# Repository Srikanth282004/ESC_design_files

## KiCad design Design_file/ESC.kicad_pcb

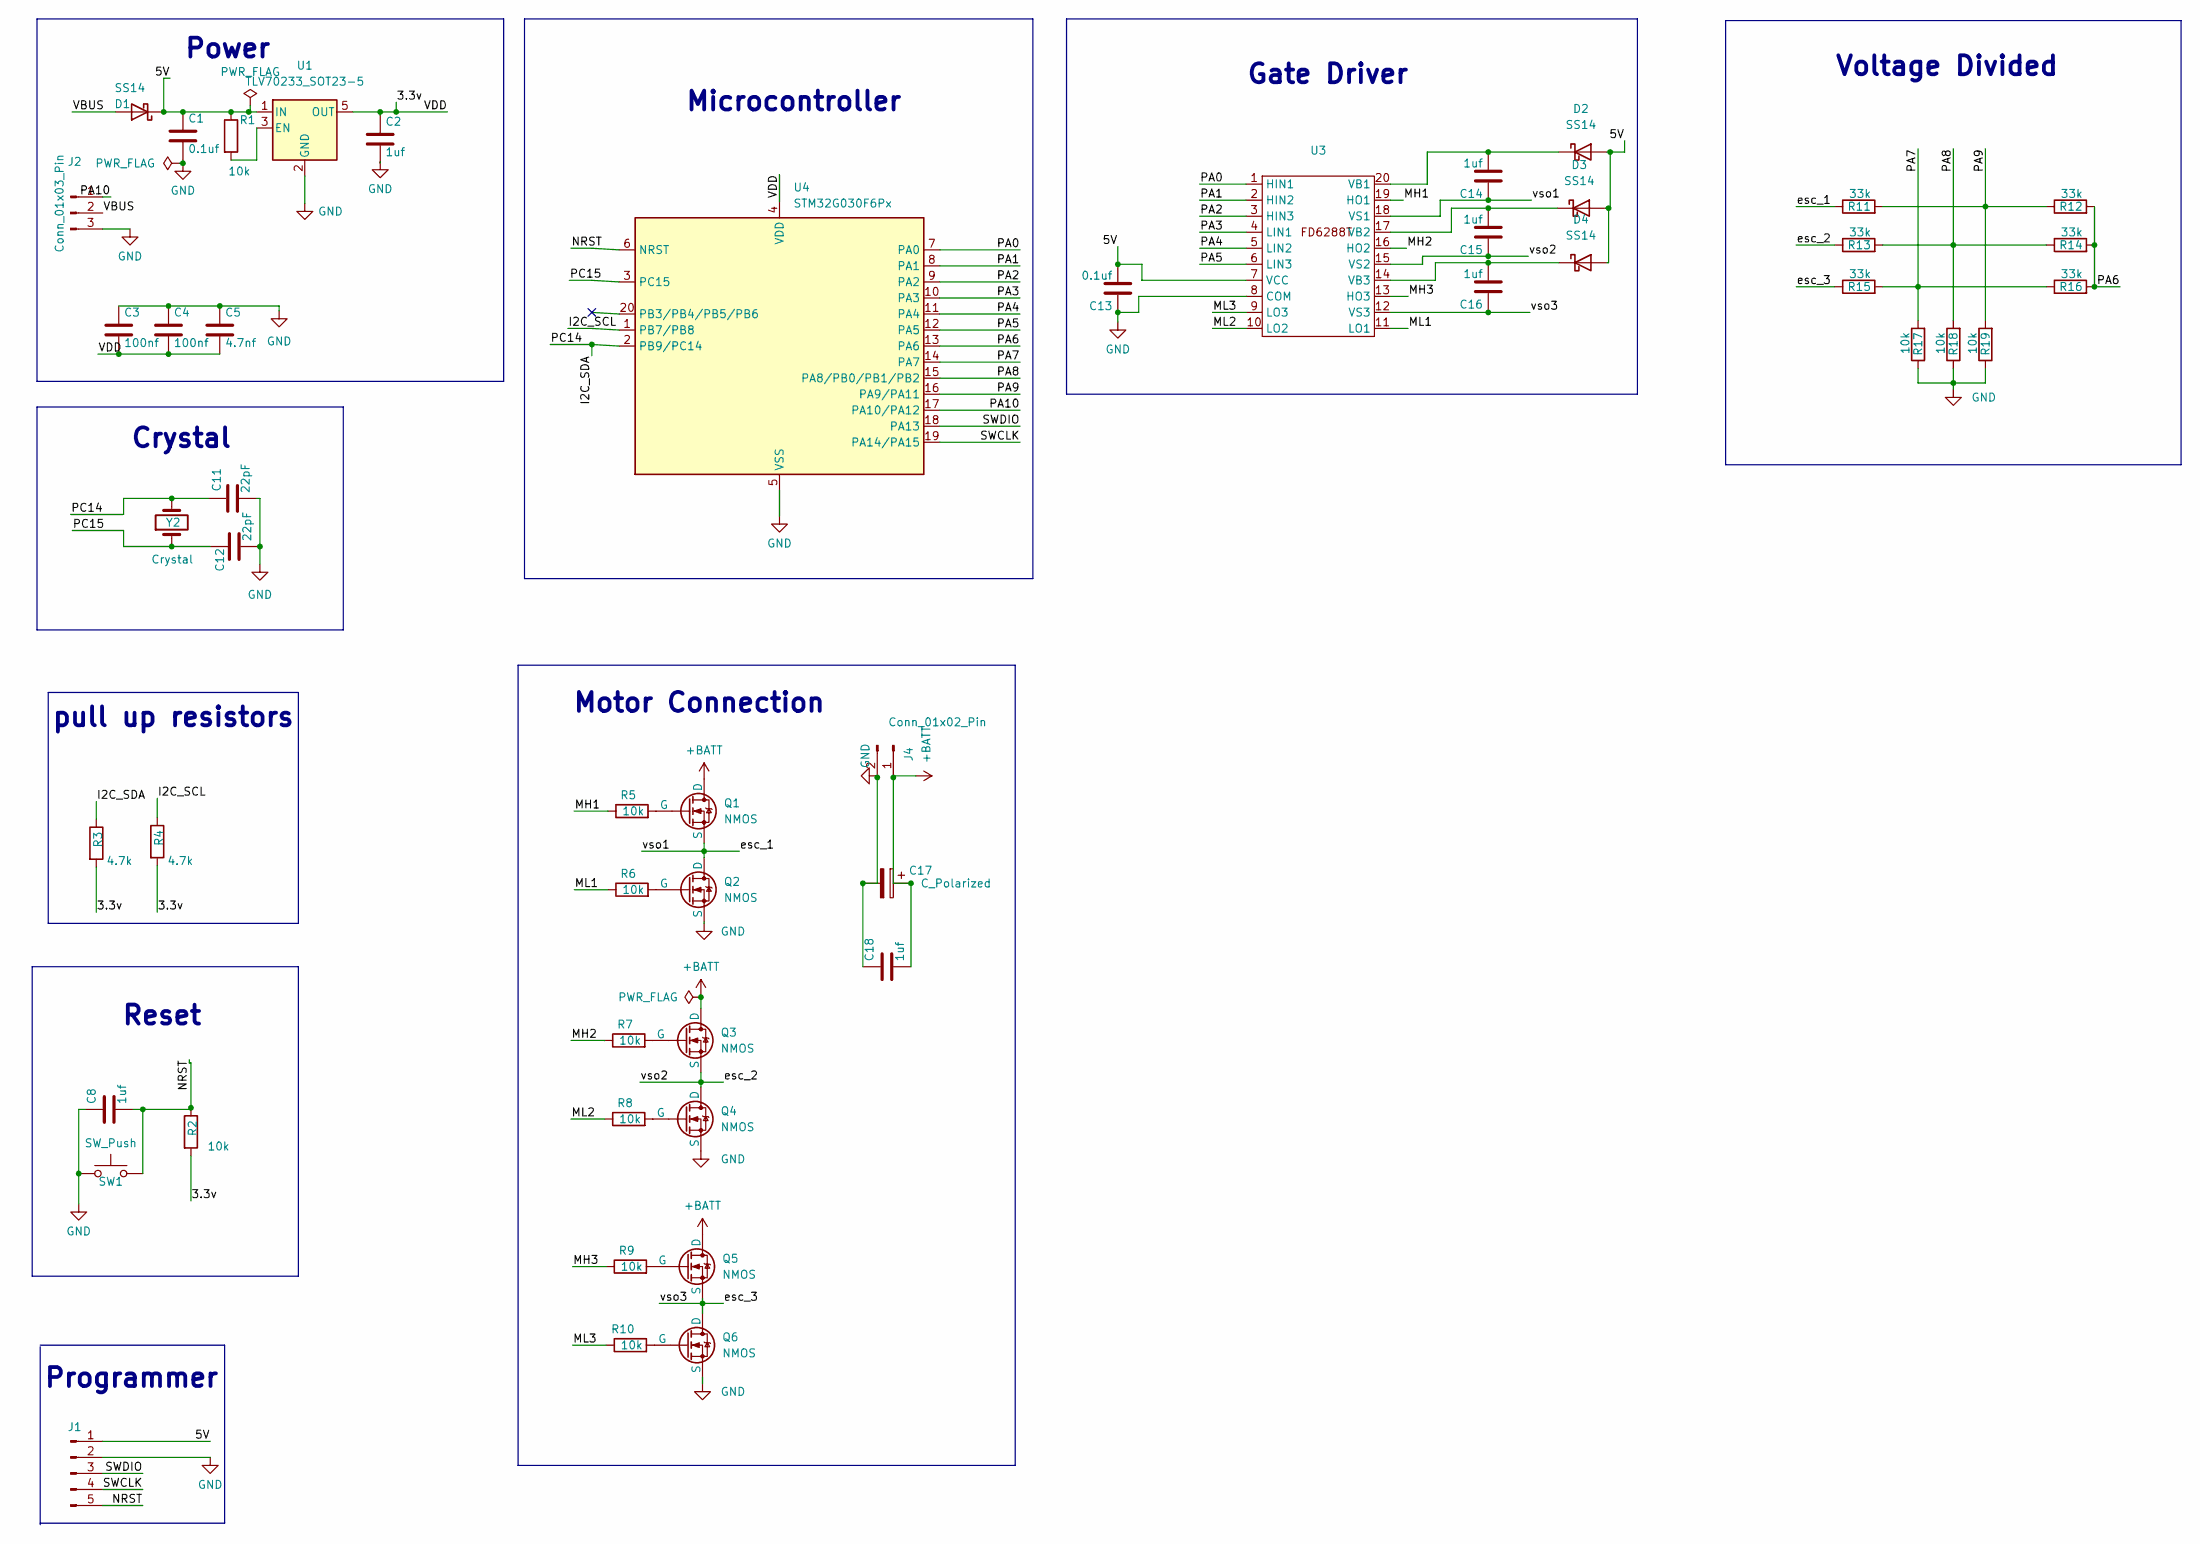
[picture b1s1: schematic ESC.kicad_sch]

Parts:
C1, C13: 0.1uf; C_0402_1005Metric_Pad0.74x0.62mm_HandSolder
C2, C8, C14, C15, C16, C18: 1uf; C_0402_1005Metric_Pad0.74x0.62mm_HandSolder
C3, C4: 100nf; C_0402_1005Metric_Pad0.74x0.62mm_HandSolder
C5: 4.7nf; C_0402_1005Metric_Pad0.74x0.62mm_HandSolder
C11, C12: 22pF; C_0402_1005Metric_Pad0.74x0.62mm_HandSolder
C17: C_Polarized; C_Elec_6.3x7.7
D1, D2, D3, D4: SS14; D_SMA
J1: Conn_01x05_Pin; 5_pin
J2: Conn_01x03_Pin; 3_pin
J4: Conn_01x02_Pin; battery_pad
Q1, Q2, Q3, Q4, Q5, Q6: NMOS; 90N03
R1, R2, R5, R6, R7, R8, R9, R10, R17, R18, R19: 10k; R_0402_1005Metric_Pad0.72x0.64mm_HandSolder
R3, R4: 4.7k; R_0402_1005Metric_Pad0.72x0.64mm_HandSolder
R11, R12, R13, R14, R15, R16: 33k; R_0402_1005Metric_Pad0.72x0.64mm_HandSolder
SW1: SW_Push; 2_PIN
U1: TLV70233_SOT23-5; SOT-23-5
U3: TSSOP-20_4.4x6.5mm_P0.65mm
U4: STM32G030F6Px; TSSOP-20_4.4x6.5mm_P0.65mm
Y2: Crystal; Crystal_SMD_0603-2Pin_6.0x3.5mm

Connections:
+BATT: C17.1, C18.2, J4.1, Q1.1 (D), Q3.1 (D), Q5.1 (D)
/3.3v: C2.1, C3.2, C4.2, C5.2, R2.2, R3.2, R4.2, U1.5 (OUT), U4.4 (VDD)
/I2C_SCL: R4.1, U4.1 (PB7/PB8)
/I2C_SDA: C11.1, R3.1, U4.2 (PB9/PC14), Y2.2
/MH1: R5.1, U3.19 (HO1)
/MH2: R7.1, U3.16 (HO2)
/MH3: R9.1, U3.13 (HO3)
/ML1: R6.1, U3.11 (LO1)
/ML2: R8.1, U3.10 (LO2)
/ML3: R10.1, U3.9 (LO3)
/NRST: C8.2, J1.5, R2.1, SW1.2, U4.6 (NRST)
/PA0: U3.1 (HIN1), U4.7 (PA0)
/PA1: U3.2 (HIN2), U4.8 (PA1)
/PA2: U3.3 (HIN3), U4.9 (PA2)
/PA3: U3.4 (LIN1), U4.10 (PA3)
/PA4: U3.5 (LIN2), U4.11 (PA4)
/PA5: U3.6 (LIN3), U4.12 (PA5)
/PA6: R12.2, R14.2, R16.2, U4.13 (PA6)
/PA7: R15.2, R16.1, R17.2, U4.14 (PA7)
/PA8: R13.2, R14.1, R18.2, U4.15 (PA8/PB0/PB1/PB2)
/PA9: R11.2, R12.1, R19.2, U4.16 (PA9/PA11)
/PA10: J2.1, U4.17 (PA10/PA12)
/PC15: C12.1, U4.3 (PC15), Y2.1
/SWCLK: J1.4, U4.19 (PA14/PA15)
/SWDIO: J1.3, U4.18 (PA13)
/VBUS: D1.2 (A), J2.2
/esc_1: C14.1, Q1.3 (S), Q2.1 (D), R11.1, U3.18 (VS1)
/esc_2: C15.1, Q3.3 (S), Q4.1 (D), R13.1, U3.15 (VS2)
/esc_3: C16.1, Q5.3 (S), Q6.1 (D), R15.1, U3.12 (VS3)
GND: C1.2, C2.2, C3.1, C4.1, C5.1, C8.1, C11.2, C12.2, C13.1, C17.2, C18.1, J1.2, J2.3, J4.2, Q2.3 (S), Q4.3 (S), Q6.3 (S), R17.1, R18.1, R19.1, SW1.1, U1.2 (GND), U3.8 (COM), U4.5 (VSS)
unnamed: C14.2, D2.1 (K), U3.20 (VB1)
unnamed: C15.2, D3.1 (K), U3.17 (VB2)
unnamed: C16.2, D4.1 (K), U3.14 (VB3)
unnamed: Q1.2 (G), R5.2
unnamed: Q2.2 (G), R6.2
unnamed: Q3.2 (G), R7.2
unnamed: Q4.2 (G), R8.2
unnamed: Q5.2 (G), R9.2
unnamed: Q6.2 (G), R10.2
unnamed: R1.2, U1.3 (EN)

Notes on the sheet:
Voltage Divided
Programmer
Microcontroller
Gate Driver
Reset
Power
Motor Connection
Crystal
pull up resistors

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
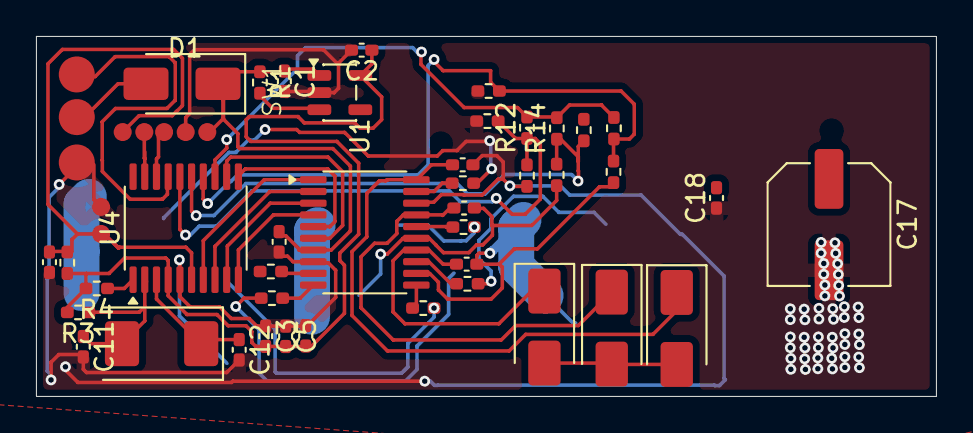
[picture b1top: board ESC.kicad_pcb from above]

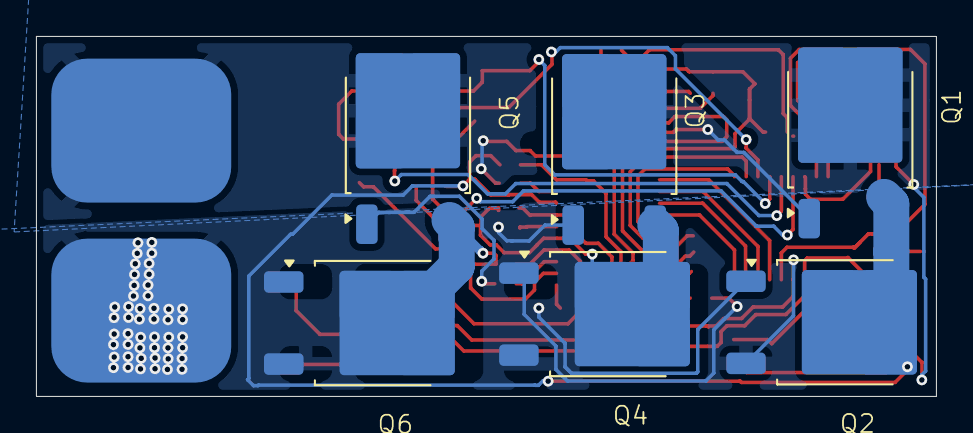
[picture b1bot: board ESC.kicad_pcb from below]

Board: 2 copper layers, 50.0 x 20.0 mm, 51 parts (7 on the bottom side), 42 nets.
